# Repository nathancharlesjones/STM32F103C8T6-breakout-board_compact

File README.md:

# STM32F103C8T6 Breakout Board - Compact

Breakout board for the venerable STM32F103C8T6 (a.k.a. the "Blue Pill") intended to be assembled by JLC PCB. For more information about this PCB and how to order one, visit [this Git repository](https://github.com/nathancharlesjones/STM32F103C8T6-breakout-board).

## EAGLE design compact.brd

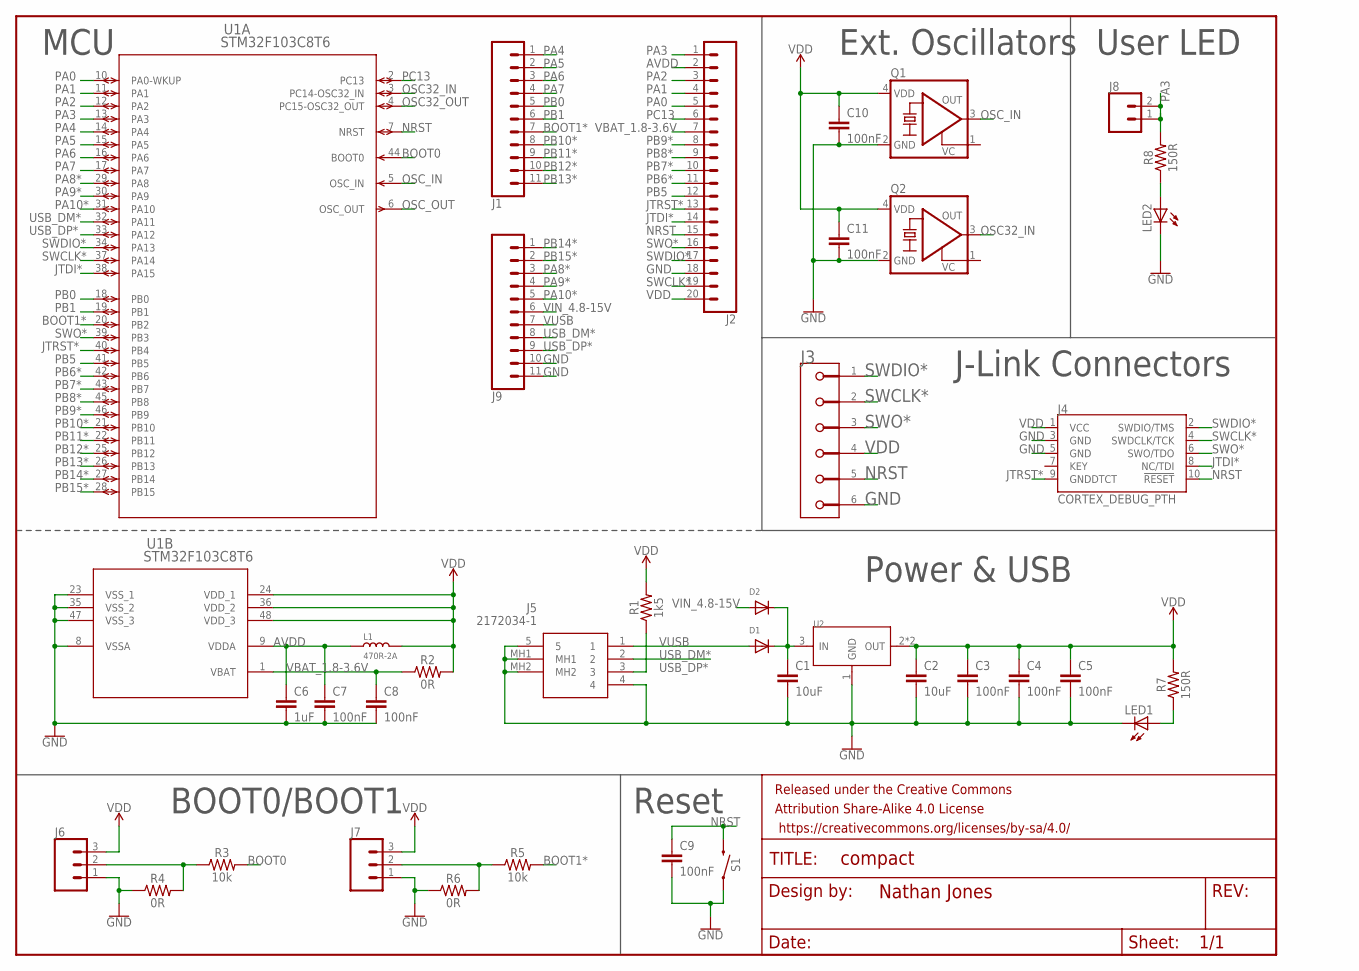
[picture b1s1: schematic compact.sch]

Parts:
C1, C2: 10uF; 0402-TIGHT; LCSC_PART C15525
C3, C4, C5, C7, C8, C9, C10, C11: 100nF; 0402-TIGHT; LCSC_PART C1525
C6: 1uF; 0402-TIGHT; LCSC_PART C52923
D1, D2: DIODESOD-123; SOD-123; LCSC_PART C8598
FRAME2: FRAME-LETTERNO_PACKAGE; DUMMY
J1, J9: CONN_111X11_NO_SILK; 1X11_NO_SILK
J2: CONN_20NOSILK; 1X20_NOSILK
J3: AVX_6-PIN_009159006061916; AVX_6-PIN_009159006061916_0
J4: CORTEX_DEBUG_PTH; 2X5-PTH-1.27MM
J5: 2172034-1; 21720341
J6, J7: CONN_031X03_NO_SILK; 1X03_NO_SILK
J8: CONN_021X02_NO_SILK; 1X02_NO_SILK
L1: 470R-2A; L0805; LCSC_PART C1015
LED1: LEDCHIPLED_0603; CHIPLED_0603; LCSC_PART C72041
LED2: LEDCHIPLED_0603; CHIPLED_0603; LCSC_PART C72038
Q1: KXO-VCXO-CMOS_4; 3.2X2.5_KXO-84-TCXO; LCSC_PART C39097
Q2: KXO-VCXO-CMOS_4; 3.2X2.5_KXO-84-TCXO; LCSC_PART C387415
R1: 1k5; 0402; LCSC_PART C25867
R2, R4, R6: 0R; 0402; LCSC_PART C17168
R3, R5: 10k; 0402; LCSC_PART C25744
R7, R8: 150R; 0402; LCSC_PART C25082
S1: MOMENTARY-SWITCH-SPST-SMD-5.2-REDUNDANT; TACTILE_SWITCH_SMD_5.2MM; LCSC_PART C318884
U1: STM32F103C8T6; LQFP48-7X7MM; LCSC_PART C94046
U2: CJT1117-3.3-SOT223; SOT-223; LCSC_PART C6186

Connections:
AVDD: C6.1, C7.1, J2.2, L1.1, U1.9 (VDDA)
BOOT0: R3.2, U1.44 (BOOT0)
BOOT1*: J1.7, R5.2, U1.20 (PB2)
GND: C1.2, C2.2, C3.2, C4.2, C5.2, C6.2, C7.2, C8.2, C9.2, C10.2, C11.2, J2.18, J3.6, J4.3 (GND), J4.5 (GND), J5.4, J5.5, J5.MH1, J5.MH2, J6.1, J7.1, J9.10, J9.11, LED1.C, LED2.C, Q1.2 (GND), Q2.2 (GND), R4.1, R6.1, S1.1, S1.2 (1), U1.8 (VSSA), U1.23 (VSS_1), U1.35 (VSS_2), U1.47 (VSS_3), U2.1 (GND)
JTDI*: J2.14, J4.8 (NC/TDI), U1.38 (PA15)
JTRST*: J2.13, J4.9 (GNDDTCT), U1.40 (PB4)
unnamed: J6.2, R3.1, R4.2
unnamed: LED2.A, R8.1
unnamed: J7.2, R5.1, R6.2
unnamed: LED1.A, R7.1
NRST: C9.1, J2.15, J3.5, J4.10 (!RESET), S1.3 (2), S1.4 (2), U1.7 (NRST)
OSC32_IN: Q2.3 (OUT), U1.3 (PC14-OSC32_IN)
OSC32_OUT: U1.4 (PC15-OSC32_OUT)
OSC_IN: Q1.3 (OUT), U1.5 (OSC_IN)
OSC_OUT: U1.6 (OSC_OUT)
PA0: J2.5, U1.10 (PA0-WKUP)
PA1: J2.4, U1.11 (PA1)
PA2: J2.3, U1.12 (PA2)
PA3: J2.1, J8.1, J8.2, R8.2, U1.13 (PA3)
PA4: J1.1, U1.14 (PA4)
PA5: J1.2, U1.15 (PA5)
PA6: J1.3, U1.16 (PA6)
PA7: J1.4, U1.17 (PA7)
PA8*: J9.3, U1.29 (PA8)
PA9*: J9.4, U1.30 (PA9)
PA10*: J9.5, U1.31 (PA10)
PB0: J1.5, U1.18 (PB0)
PB1: J1.6, U1.19 (PB1)
PB5: J2.12, U1.41 (PB5)
PB6*: J2.11, U1.42 (PB6)
PB7*: J2.10, U1.43 (PB7)
PB8*: J2.9, U1.45 (PB8)
PB9*: J2.8, U1.46 (PB9)
PB10*: J1.8, U1.21 (PB10)
PB11*: J1.9, U1.22 (PB11)
PB12*: J1.10, U1.25 (PB12)
PB13*: J1.11, U1.26 (PB13)
PB14*: J9.1, U1.27 (PB14)
PB15*: J9.2, U1.28 (PB15)
PC13: J2.6, U1.2 (PC13)
SWCLK*: J2.19, J3.2, J4.4 (SWDCLK/TCK), U1.37 (PA14)
SWDIO*: J2.17, J3.1, J4.2 (SWDIO/TMS), U1.34 (PA13)
SWO*: J2.16, J3.3, J4.6 (SWO/TDO), U1.39 (PB3)
USB_DM*: J5.2, J9.8, U1.32 (PA11)
USB_DP*: J5.3, J9.9, R1.1, U1.33 (PA12)
VBAT_1.8-3.6V: C8.1, J2.7, R2.1, U1.1 (VBAT)
VDD: C2.1, C3.1, C4.1, C5.1, C10.1, C11.1, J2.20, J3.4, J4.1 (VCC), J6.3, J7.3, L1.2, Q1.4 (VDD), Q2.4 (VDD), R1.2, R2.2, R7.2, U1.24 (VDD_1), U1.36 (VDD_2), U1.48 (VDD_3), U2.2 (OUT), U2.TER (OUT)
VIN: C1.1, D1.C, D2.C, U2.3 (IN)
VIN_4.8-15V: D2.A, J9.6
VUSB: D1.A, J5.1, J9.7

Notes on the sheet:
MCU
Power & USB
Reset
BOOT0/BOOT1
Ext. Oscillators
User LED
J-Link Connectors

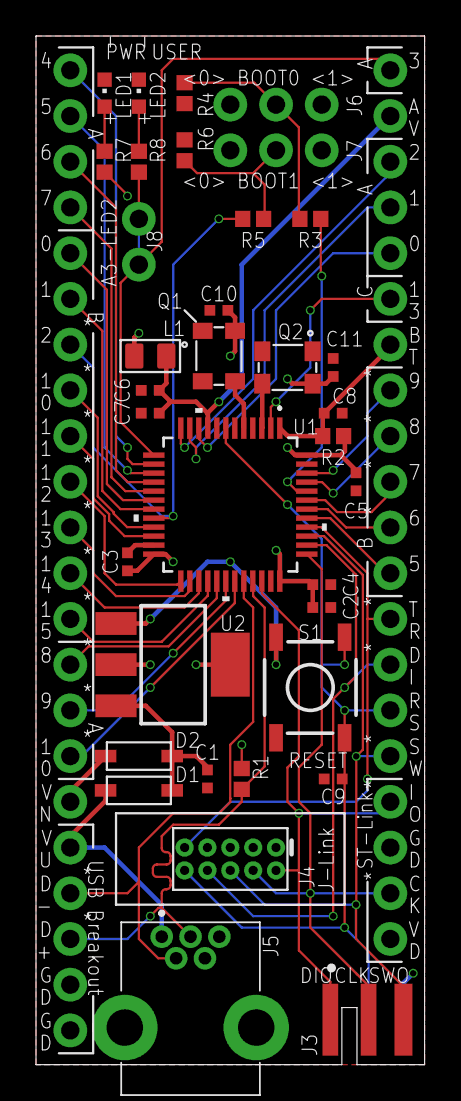
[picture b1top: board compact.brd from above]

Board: 2 copper layers, 21.6 x 57.1 mm, 39 parts (0 on the bottom side), 48 nets.

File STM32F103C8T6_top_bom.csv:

Comment,Designator,Footprint,LCSC Part #
0R,D1 D2 LED1 LED2 Q1 Q2 R2 R5 R7,R0402,C17168
1k5,R1,R0402,C25867
1uF,C6,C0402,C52923
10k,R4 R6,R0402,C25744
10uF,C1 C2,C0402,C15525
100R,R8 R9,R0402,C25076
100nF,C3 C4 C5 C7 C8 C9 C10 C12,C0402,C1525
10118193-0001LF,USB1,MICRO-USB5+6P-SMD-0.65-B,
AVX_009159010061916AVX_009159010061916_0_0,J3,AVX_009159010061916_0,
CJT1117-3.3-SOT223,U2,SOT-223,C6186
MOMENTARY-SWITCH-SPST-SMD-5.2-REDUNDANT,S1,TACTILE_SWITCH_SMD_5.2MM,C318884
STM32F103C8T6,U1,LQFP48-7X7MM,C94046

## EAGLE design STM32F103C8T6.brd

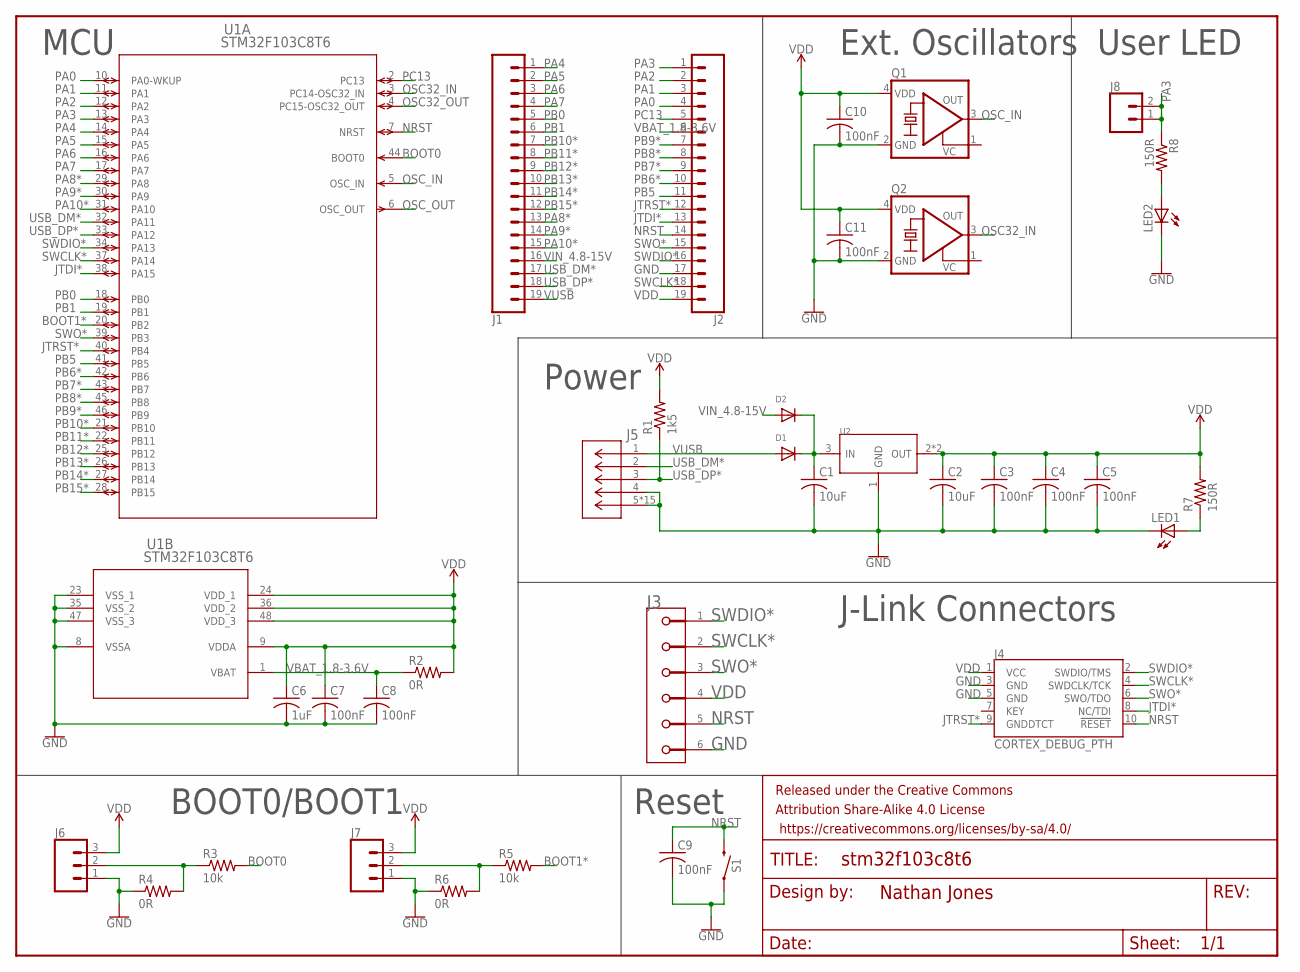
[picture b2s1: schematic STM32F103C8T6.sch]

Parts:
C1, C2: 10uF; C0402; LCSC_PART C15525
C3, C4, C5, C7, C8, C9, C10, C11: 100nF; C0402; LCSC_PART C1525
C6: 1uF; C0402; LCSC_PART C52923
D1, D2: DIODESOD-123; SOD-123; LCSC_PART C8598
FRAME2: FRAME-LETTERNO_PACKAGE; DUMMY
J1, J2: CONN_191X19_NO_SILK; 1X19_NO_SILK
J3: AVX_6-PIN_009159006061916; AVX_6-PIN_009159006061916_0
J4: CORTEX_DEBUG_PTH; 2X5-PTH-1.27MM
J5: 10118194-0001LF; CONN_10118194-0001LF_AMP
J6, J7: CONN_031X03_NO_SILK; 1X03_NO_SILK
J8: CONN_021X02_NO_SILK; 1X02_NO_SILK
LED1: LEDCHIPLED_0603; CHIPLED_0603; LCSC_PART C72041
LED2: LEDCHIPLED_0603; CHIPLED_0603; LCSC_PART C72038
Q1: KXO-VCXO-CMOS_4; 3.2X2.5_KXO-84-TCXO; LCSC_PART C39097
Q2: KXO-VCXO-CMOS_4; 3.2X2.5_KXO-84-TCXO; LCSC_PART C387415
R1: 1k5; R0402; LCSC_PART C25867
R2, R4, R6: 0R; R0402; LCSC_PART C17168
R3, R5: 10k; R0402; LCSC_PART C25744
R7, R8: 150R; R0402; LCSC_PART C25082
S1: MOMENTARY-SWITCH-SPST-SMD-5.2-REDUNDANT; TACTILE_SWITCH_SMD_5.2MM; LCSC_PART C318884
U1: STM32F103C8T6; LQFP48-7X7MM; LCSC_PART C94046
U2: CJT1117-3.3-SOT223; SOT-223; LCSC_PART C6186

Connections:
BOOT0: R3.2, U1.44 (BOOT0)
BOOT1*: R5.2, U1.20 (PB2)
GND: C1.2, C2.2, C3.2, C4.2, C5.2, C6.2, C7.2, C8.2, C9.2, C10.2, C11.2, J2.17, J3.6, J4.3 (GND), J4.5 (GND), J5.4, J5.5, J5.10 (5), J5.11 (5), J5.S_1 (5), J5.S_1_H1 (5), J5.S_1_H2 (5), J5.S_2 (5), J5.S_2_H1 (5), J5.S_2_H2 (5), J5.S_3 (5), J5.S_3_H1 (5), J5.S_3_H2 (5), J5.S_4 (5), J5.S_4_H1 (5), J5.S_4_H2 (5), J6.1, J7.1, LED1.C, LED2.C, Q1.2 (GND), Q2.2 (GND), R4.1, R6.1, S1.1, S1.2 (1), U1.8 (VSSA), U1.23 (VSS_1), U1.35 (VSS_2), U1.47 (VSS_3), U2.1 (GND)
JTDI*: J2.13, J4.8 (NC/TDI), U1.38 (PA15)
JTRST*: J2.12, J4.9 (GNDDTCT), U1.40 (PB4)
unnamed: J6.2, R3.1, R4.2
unnamed: LED2.A, R8.2
unnamed: J7.2, R5.1, R6.2
unnamed: LED1.A, R7.1
NRST: C9.1, J2.14, J3.5, J4.10 (!RESET), S1.3 (2), S1.4 (2), U1.7 (NRST)
OSC32_IN: Q2.3 (OUT), U1.3 (PC14-OSC32_IN)
OSC32_OUT: U1.4 (PC15-OSC32_OUT)
OSC_IN: Q1.3 (OUT), U1.5 (OSC_IN)
OSC_OUT: U1.6 (OSC_OUT)
PA0: J2.4, U1.10 (PA0-WKUP)
PA1: J2.3, U1.11 (PA1)
PA2: J2.2, U1.12 (PA2)
PA3: J2.1, J8.1, J8.2, R8.1, U1.13 (PA3)
PA4: J1.1, U1.14 (PA4)
PA5: J1.2, U1.15 (PA5)
PA6: J1.3, U1.16 (PA6)
PA7: J1.4, U1.17 (PA7)
PA8*: J1.13, U1.29 (PA8)
PA9*: J1.14, U1.30 (PA9)
PA10*: J1.15, U1.31 (PA10)
PB0: J1.5, U1.18 (PB0)
PB1: J1.6, U1.19 (PB1)
PB5: J2.11, U1.41 (PB5)
PB6*: J2.10, U1.42 (PB6)
PB7*: J2.9, U1.43 (PB7)
PB8*: J2.8, U1.45 (PB8)
PB9*: J2.7, U1.46 (PB9)
PB10*: J1.7, U1.21 (PB10)
PB11*: J1.8, U1.22 (PB11)
PB12*: J1.9, U1.25 (PB12)
PB13*: J1.10, U1.26 (PB13)
PB14*: J1.11, U1.27 (PB14)
PB15*: J1.12, U1.28 (PB15)
PC13: J2.5, U1.2 (PC13)
SWCLK*: J2.18, J3.2, J4.4 (SWDCLK/TCK), U1.37 (PA14)
SWDIO*: J2.16, J3.1, J4.2 (SWDIO/TMS), U1.34 (PA13)
SWO*: J2.15, J3.3, J4.6 (SWO/TDO), U1.39 (PB3)
USB_DM*: J1.17, J5.2, U1.32 (PA11)
USB_DP*: J1.18, J5.3, R1.1, U1.33 (PA12)
VBAT_1.8-3.6V: C8.1, J2.6, R2.1, U1.1 (VBAT)
VDD: C2.1, C3.1, C4.1, C5.1, C6.1, C7.1, C10.1, C11.1, J2.19, J3.4, J4.1 (VCC), J6.3, J7.3, Q1.4 (VDD), Q2.4 (VDD), R1.2, R2.2, R7.2, U1.9 (VDDA), U1.24 (VDD_1), U1.36 (VDD_2), U1.48 (VDD_3), U2.2 (OUT), U2.TER (OUT)
VIN: C1.1, D1.C, D2.C, U2.3 (IN)
VIN_4.8-15V: D2.A, J1.16
VUSB: D1.A, J1.19, J5.1

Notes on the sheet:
MCU
Power
Reset
BOOT0/BOOT1
Ext. Oscillators
User LED
J-Link Connectors

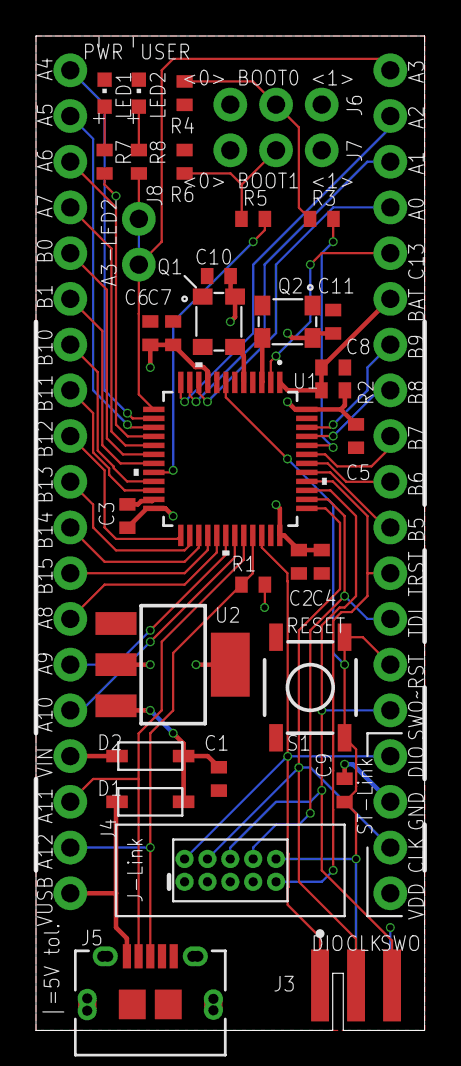
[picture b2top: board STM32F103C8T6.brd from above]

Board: 2 copper layers, 21.6 x 55.2 mm, 37 parts (0 on the bottom side), 47 nets.

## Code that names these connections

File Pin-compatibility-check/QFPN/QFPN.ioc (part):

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Mcu.Name=STM32F103CBUx
Mcu.Package=UFQFPN48
Mcu.UserName=STM32F103CBUx
PA11.Mode=Device
PA11.Signal=USB_DM
PA12.Mode=Device
PA12.Signal=USB_DP
PA13.Mode=JTAG_5_pins
PA13.Signal=SYS_JTMS-SWDIO
PA14.Mode=JTAG_5_pins
PA14.Signal=SYS_JTCK-SWCLK
PA15.Mode=JTAG_5_pins
PA15.Signal=SYS_JTDI
PB3.Mode=JTAG_5_pins
PB3.Signal=SYS_JTDO-TRACESWO
PB4.Mode=JTAG_5_pins
PB4.Signal=SYS_NJTRST
PC14-OSC32_IN.Mode=LSE-External-Clock-Source
PC14-OSC32_IN.Signal=RCC_OSC32_IN
PC15-OSC32_OUT.Mode=LSE-External-Clock-Source
PC15-OSC32_OUT.Signal=RCC_OSC32_OUT
PD0-OSC_IN.Mode=HSE-External-Clock-Source
PD0-OSC_IN.Signal=RCC_OSC_IN
PD1-OSC_OUT.Mode=HSE-External-Clock-Source
PD1-OSC_OUT.Signal=RCC_OSC_OUT
board=custom

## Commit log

2020-12-20 Copied over STM32F0 schematic. Updated MCU and several other components.
2020-12-21 Added power capacitors. Added new LSE oscillator.
2020-12-22 Nearly finalized circuit.
2020-12-28 Nearly finished layout.
2020-12-30 Finished layout.
2021-01-02 Updated files.
2021-01-02 Renamed files.
2021-01-02 Removed libraries, Reference, and Pin-Compatibility-Check folders.
2021-01-02 Removed _todo.md
2021-01-04 Added screenshots.
2021-01-05 Updated screenshots.
2021-01-05 Updated README.
2021-01-30 Changed USB connector to mini-B. Change pin labels on the silkscreen to be more readable.
2021-01-30 Updated AVX footprint.
2021-02-15 Separated Standard configuration into Standard-no-HSE and Standard-with-HSE configurations.
2021-03-05 Updated Debug Edge library. Updated Gerbers, screenshots, and schematic image. Switched to new Mini-B USB footprint.
2021-03-08 Added pictures.

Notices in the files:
parts and their libraries:
SparkFun-Connectors: Licensing: Creative Commons ShareAlike 4.0 International - https://creativecommons.org/licenses/by-sa/4.0
crystal-geyer_V1_0: Copyright: Geyer-Electronic
COPYRIGHT: Copyright (C) 2018 Accelerated Designs. All rights reserved
